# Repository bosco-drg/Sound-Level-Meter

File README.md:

# Sonomètre — Projet de mesure de niveau sonore

> Projet complet de sonomètre électronique : schéma, PCB (KiCad) et simulations (LTSpice).

---

## Aperçu rapide

Ce dépôt contient la conception d'un **sonomètre** (instrument de mesure du niveau sonore) couvrant l'adaptation d'entrée, la conditionnement du signal, le filtrage, la détection RMS/Crête, l'acquisition et les aspects matériels (schéma et PCB). Sont inclus : le **schéma**, le **PCB** et les **simulations**.

### Points clés

- **Mesure de niveau sonore** : détection RMS et/ou crête, calcul de niveaux (dB SPL)
- **Pondérations et filtres** : options de filtrage (pondération A/B) pour mesures conforme
- **Calibration** : procédures et composants pour calibration avec source connue
- **Conception matérielle** : schéma et routage PCB sous KiCad
- **Simulations** : modèles LTSpice pour valider le conditionnement et la détection
- **Documentation visuelle** : diagrammes fonctionnels et captures de simulation

---

## PCB

<div align="center">

**PCB — côté composants**

</div>

<div align="center">

**PCB — verso**

</div>

---

## Structure du projet

```
Sound-Level-Meter/
├── README.md
├── doc/                       # Documentation visuelle et images
├── schematic_Kicad/           # Projet KiCad (schéma + PCB)
│   └── Projet2_EC/
│       ├── Projet2_EC.kicad_sch
│       ├── Projet2_EC.kicad_pcb
│       └── fp-info-cache/
└── simulation/
	└── sound_level_meter_SPICE.asc
```

---

## Ouvrir le projet

### KiCad
- Ouvrir le projet dans [schematic_Kicad/Projet2_EC/](schematic_Kicad/Projet2_EC/)
- Fichiers principaux :
	- Schéma : [schematic_Kicad/Projet2_EC/Projet2_EC.kicad_sch](schematic_Kicad/Projet2_EC/Projet2_EC.kicad_sch)
	- PCB : [schematic_Kicad/Projet2_EC/Projet2_EC.kicad_pcb](schematic_Kicad/Projet2_EC/Projet2_EC.kicad_pcb)

### LTSpice
- Schéma de simulation : [simulation/sound_level_meter_SPICE.asc](simulation/sound_level_meter_SPICE.asc)

---

## Auteurs

- **Bosco de Rauglaudre**
- **Titouan Bocquet**
- **Gavin Mac Aonghusa**

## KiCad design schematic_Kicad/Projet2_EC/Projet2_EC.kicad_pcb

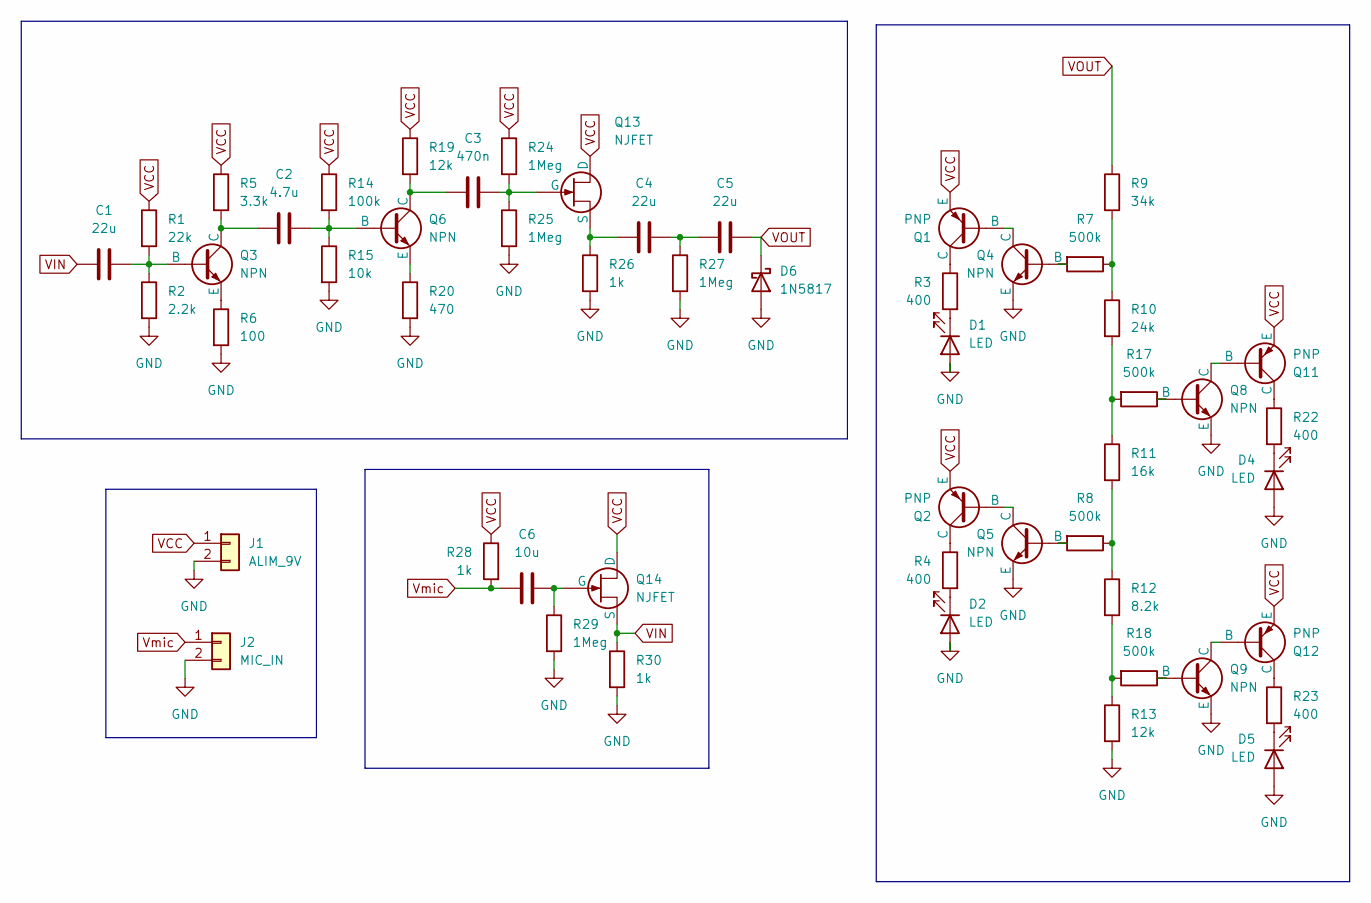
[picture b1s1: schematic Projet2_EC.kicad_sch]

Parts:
C1, C4, C5: 22u; CP_Radial_D5.0mm_P2.50mm
C2: 4.7u; CP_Radial_D5.0mm_P2.00mm
C3: 470n; C_Rect_L7.2mm_W2.5mm_P5.00mm
C6: 10u; CP_Radial_D5.0mm_P2.50mm
D1, D2, D4, D5: LED; LED_D5.0mm
D6: 1N5817; D_DO-41_SOD81_P10.16mm_Horizontal
J1: ALIM_9V; TerminalBlock_CUI_TB007-508-02_1x02_P5.08mm_Horizontal
J2: MIC_IN; TerminalBlock_CUI_TB007-508-02_1x02_P5.08mm_Horizontal
Q1, Q2, Q11, Q12: PNP; TO-18-3
Q3, Q4, Q5, Q6, Q8, Q9: NPN; TO-18-3
Q13, Q14: NJFET; TO-92_Inline
R1: 22k; R_Axial_DIN0207_L6.3mm_D2.5mm_P7.62mm_Horizontal
R2: 2.2k; R_Axial_DIN0207_L6.3mm_D2.5mm_P7.62mm_Horizontal
R3, R4, R22, R23: 400; R_Axial_DIN0207_L6.3mm_D2.5mm_P7.62mm_Horizontal
R5: 3.3k; R_Axial_DIN0207_L6.3mm_D2.5mm_P7.62mm_Horizontal
R6: 100; R_Axial_DIN0207_L6.3mm_D2.5mm_P7.62mm_Horizontal
R7, R8, R17, R18: 500k; R_Axial_DIN0207_L6.3mm_D2.5mm_P7.62mm_Horizontal
R9: 34k; R_Axial_DIN0207_L6.3mm_D2.5mm_P7.62mm_Horizontal
R10: 24k; R_Axial_DIN0207_L6.3mm_D2.5mm_P7.62mm_Horizontal
R11: 16k; R_Axial_DIN0207_L6.3mm_D2.5mm_P7.62mm_Horizontal
R12: 8.2k; R_Axial_DIN0207_L6.3mm_D2.5mm_P7.62mm_Horizontal
R13, R19: 12k; R_Axial_DIN0207_L6.3mm_D2.5mm_P7.62mm_Horizontal
R14: 100k; R_Axial_DIN0207_L6.3mm_D2.5mm_P7.62mm_Horizontal
R15: 10k; R_Axial_DIN0207_L6.3mm_D2.5mm_P7.62mm_Horizontal
R20: 470; R_Axial_DIN0207_L6.3mm_D2.5mm_P7.62mm_Horizontal
R24, R25, R27, R29: 1Meg; R_Axial_DIN0207_L6.3mm_D2.5mm_P7.62mm_Horizontal
R26, R28, R30: 1k; R_Axial_DIN0207_L6.3mm_D2.5mm_P7.62mm_Horizontal

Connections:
GND: D1.2 (A), D2.2 (A), D4.2 (A), D5.2 (A), D6.2 (A), J1.2, J2.2, Q4.3 (E), Q5.3 (E), Q8.3 (E), Q9.3 (E), R2.2, R6.2, R13.2, R15.2, R20.2, R25.2, R26.2, R27.2, R29.2, R30.2
unnamed: C4.2, C5.1, R27.1
unnamed: D1.1 (K), R3.2
unnamed: D2.1 (K), R4.2
unnamed: D4.1 (K), R22.2
unnamed: D5.1 (K), R23.2
unnamed: Q1.2 (B), Q4.1 (C)
unnamed: Q1.1 (C), R3.1
unnamed: Q2.2 (B), Q5.1 (C)
unnamed: Q2.1 (C), R4.1
unnamed: C1.2, Q3.2 (B), R1.2, R2.1
unnamed: C2.1, Q3.1 (C), R5.2
unnamed: Q3.3 (E), R6.1
unnamed: Q4.2 (B), R7.2
unnamed: Q5.2 (B), R8.2
unnamed: C2.2, Q6.2 (B), R14.2, R15.1
unnamed: C3.1, Q6.1 (C), R19.2
unnamed: Q6.3 (E), R20.1
unnamed: Q8.2 (B), R17.1
unnamed: Q9.2 (B), R18.1
unnamed: Q8.1 (C), Q11.2 (B)
unnamed: Q11.1 (C), R22.1
unnamed: Q9.1 (C), Q12.2 (B)
unnamed: Q12.1 (C), R23.1
unnamed: C3.2, Q13.2 (G), R24.2, R25.1
unnamed: C4.1, Q13.3 (S), R26.1
unnamed: C6.2, Q14.2 (G), R29.1
unnamed: R7.1, R9.2, R10.1
unnamed: R10.2, R11.1, R17.2
unnamed: R8.1, R11.2, R12.1
unnamed: R12.2, R13.1, R18.2
VCC: J1.1, Q1.3 (E), Q2.3 (E), Q11.3 (E), Q12.3 (E), Q13.1 (D), Q14.1 (D), R1.1, R5.1, R14.1, R19.1, R24.1, R28.1
VIN: C1.1, Q14.3 (S), R30.1
VOUT: C5.2, D6.1 (K), R9.1
Vmic: C6.1, J2.1, R28.2

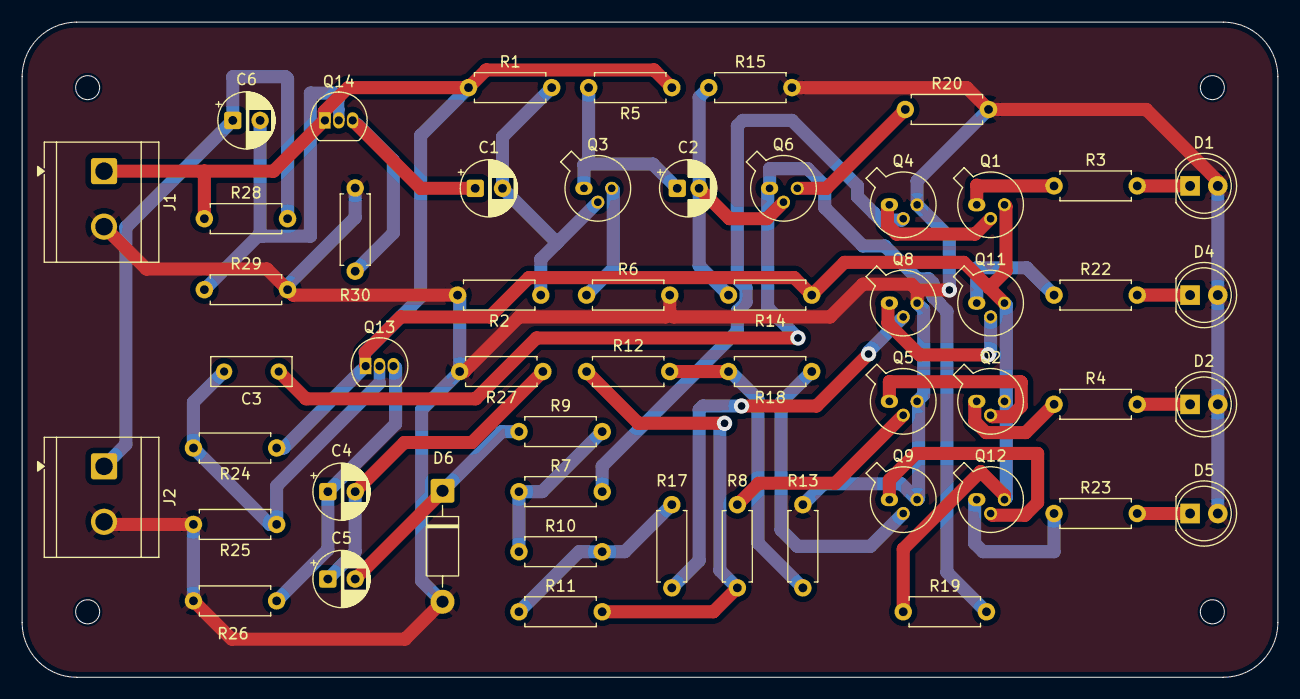
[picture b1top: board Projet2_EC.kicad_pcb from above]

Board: 2 copper layers, 115.0 x 60.0 mm, 53 parts (0 on the bottom side), 35 nets.

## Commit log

2026-05-27 Sonometer projet
2026-05-27 mise a jour du readme
2026-05-27 mise a jour du README.md
